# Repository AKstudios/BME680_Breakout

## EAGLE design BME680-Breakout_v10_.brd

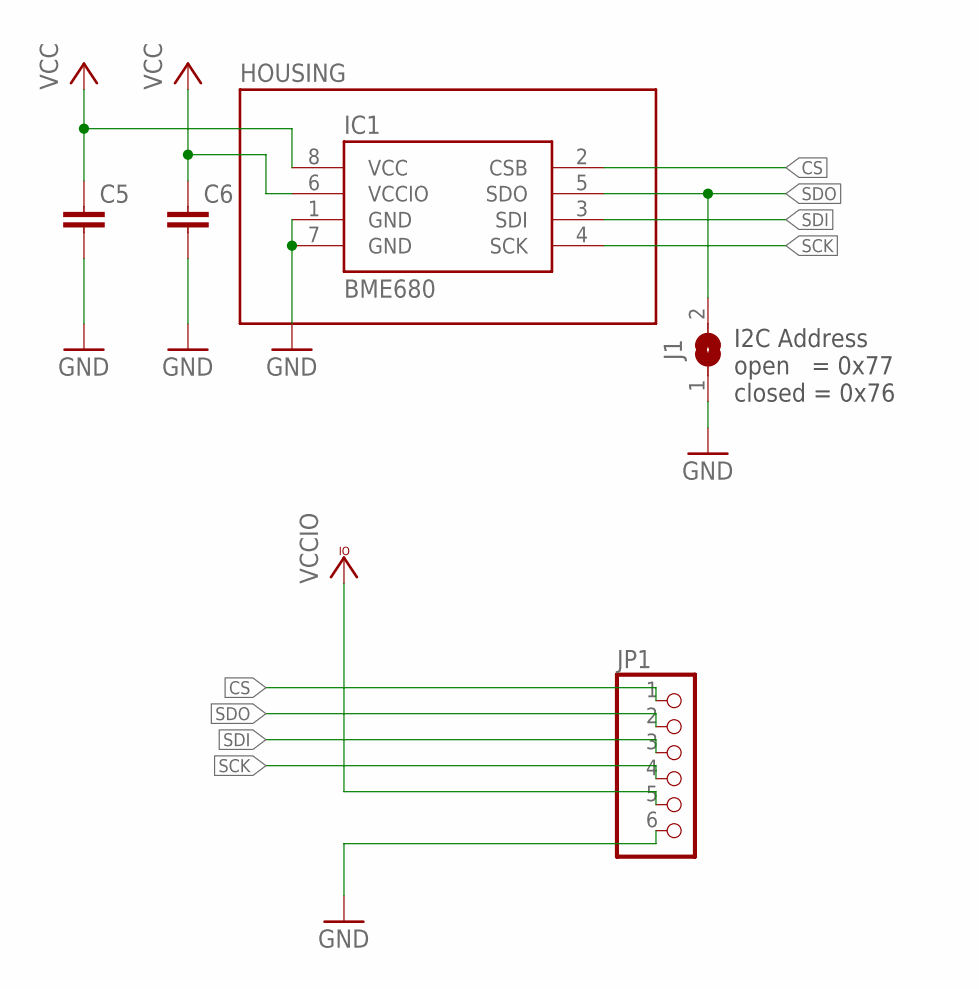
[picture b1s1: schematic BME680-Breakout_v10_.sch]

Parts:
C5, C6: CAP0805; 0805
HOUSING: SF2
IC1: BME680
J1: JUMPER2-0603
JP1: PINHD-1X6; 1X06

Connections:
CS: IC1.2 (CSB), JP1.1
GND: C5.2, C6.2, IC1.1 (GND), IC1.7 (GND), J1.1, JP1.6
SCK: IC1.4 (SCK), JP1.4
SDI: IC1.3 (SDI), JP1.3
SDO: IC1.5 (SDO), J1.2, JP1.2
VCC: C5.1, C6.1, IC1.6 (VCCIO), IC1.8 (VCC), JP1.5

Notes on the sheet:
I2C Address open = 0x77 closed = 0x76

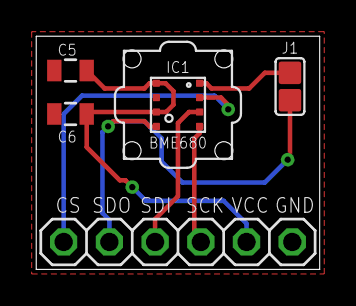
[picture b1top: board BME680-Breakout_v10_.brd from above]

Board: 2 copper layers, 15.7 x 13.0 mm, 6 parts (0 on the bottom side), 6 nets.

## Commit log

2017-09-14 :circus_tent: Added .gitattributes & .gitignore files
2017-09-14 init

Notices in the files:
parts and their libraries:
SparkFun-Passives: Licensing: Creative Commons ShareAlike 4.0 International - https://creativecommons.org/licenses/by-sa/4.0
